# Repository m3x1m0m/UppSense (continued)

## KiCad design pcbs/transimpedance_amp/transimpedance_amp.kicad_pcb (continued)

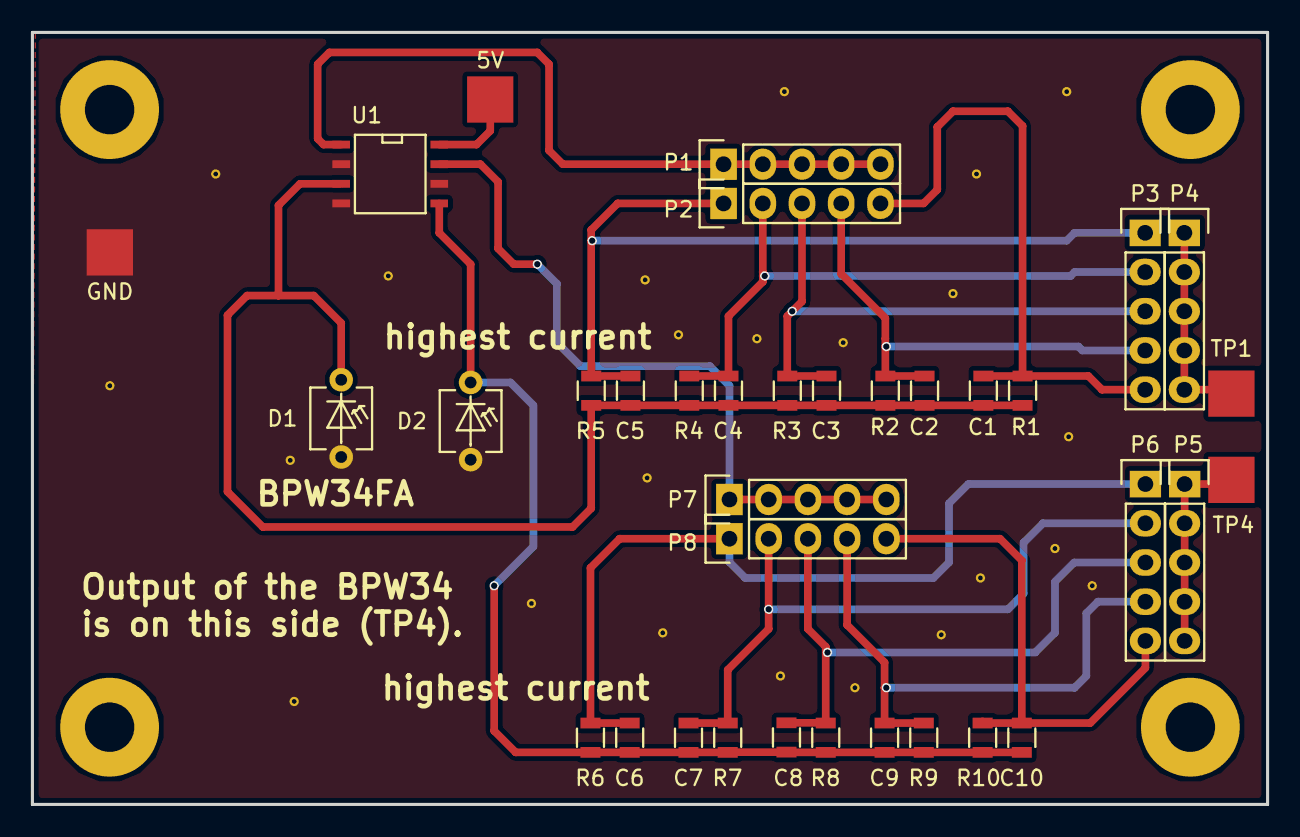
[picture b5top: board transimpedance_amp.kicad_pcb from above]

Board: 2 copper layers, 80.0 x 50.0 mm, 35 parts (0 on the bottom side), 18 nets.

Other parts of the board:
5V: TEST; TP_SMD_quadr_3mm
GND: TEST; TP_SMD_quadr_3mm

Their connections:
+5V: 5V.1; also elsewhere on the board
GND: GND.1; also elsewhere on the board

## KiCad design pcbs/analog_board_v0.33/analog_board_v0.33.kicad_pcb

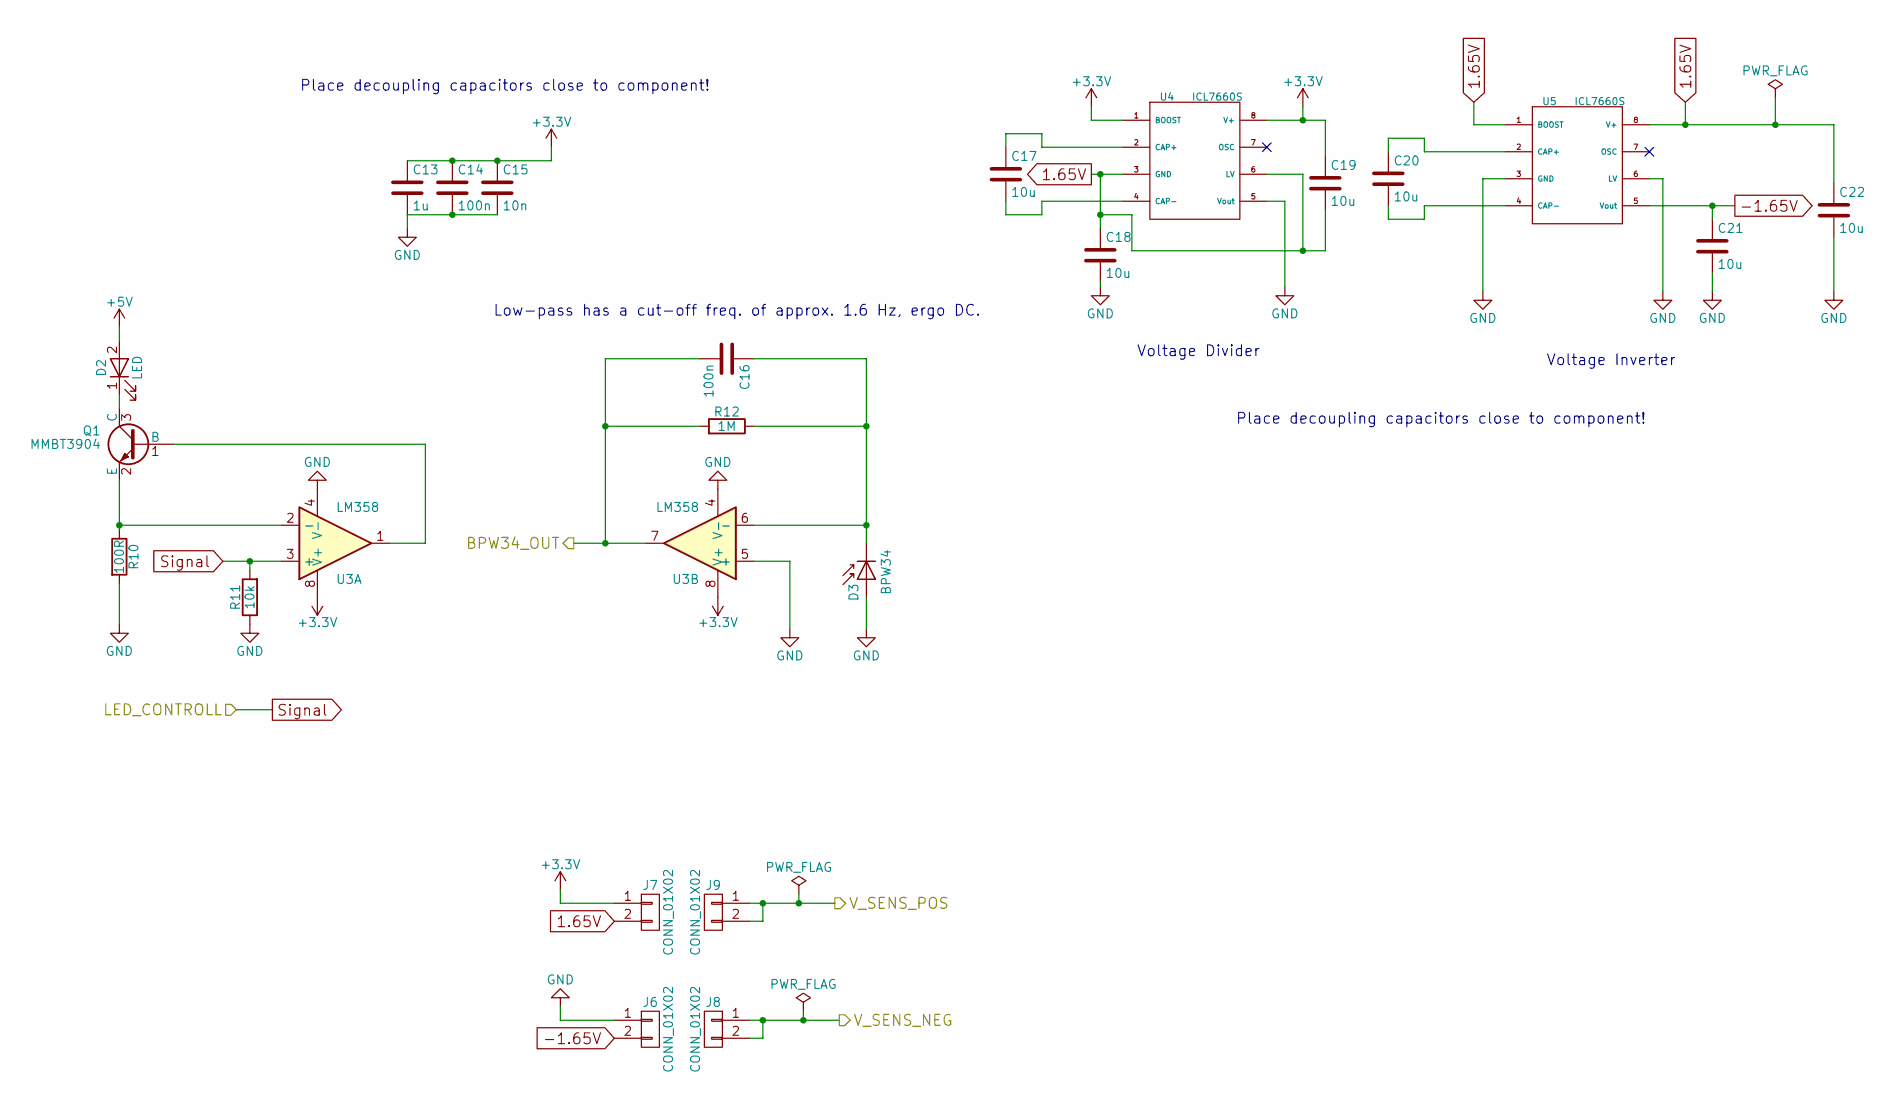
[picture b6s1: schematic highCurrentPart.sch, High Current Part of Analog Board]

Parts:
C13: 1u; R_0805; Farnell 2496946
C14, C16: 100n; R_0805; Farnell 499687
C15: 10n; R_0805; Farnell 1414662
C17, C18, C19, C20, C21, C22: 10u; R_0805; Farnell 1833812
D2: LED; LED_D5.0mm
D3: BPW34; BPW34FA; Farnell 1045425
J6, J7, J8, J9: CONN_01X02; Samtec-PHT-1-2-01-L-S
Q1: MMBT3904; SOT-23; Farnell 1757935
R10: 100R; R_0805; Farnell 9237364
R11: 10k; R_0805; Farnell 9237755
R12: 1M; R_0805; Farnell 1576507
U3: LM358; SOIC-8-N; Farnell 1564331
U4, U5: ICL7660S; SOIC-8-N; Farnell 1561969

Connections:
1.65V: C18.1, C19.2, C22.1, J7.2, U4.3 (GND), U4.6 (LV), U5.1 (BOOST), U5.8 (V+)
+3V3: C13.1, C14.1, C15.1, C19.1, J7.1, U3.8 (V+), U4.1 (BOOST), U4.8 (V+); also elsewhere on the board
+5V: D2.2 (A); also elsewhere on the board
-1.65V: C21.1, J6.2, U5.5 (Vout)
/highCurrentPart/V_SENS_NEG: J8.1, J8.2; also elsewhere on the board
/highCurrentPart/V_SENS_POS: J9.1, J9.2; also elsewhere on the board
/interface/ADC4: C16.2, R12.2, U3.7; also elsewhere on the board
GND: C13.2, C14.2, C15.2, C18.2, C21.2, C22.2, D3.2 (A), J6.1, R10.2, R11.1, U3.4 (V-), U3.5 (+), U4.5 (Vout), U5.3 (GND), U5.6 (LV); also elsewhere on the board
unnamed: C16.1, D3.1 (K), R12.1, U3.6 (-)
unnamed: C17.1, U4.2 (CAP+)
unnamed: C17.2, U4.4 (CAP-)
unnamed: C20.1, U5.2 (CAP+)
unnamed: C20.2, U5.4 (CAP-)
unnamed: D2.1 (K), Q1.3 (C)
unnamed: Q1.1 (B), U3.1
unnamed: Q1.2 (E), R10.1, U3.2 (-)
Signal: R11.2, U3.3 (+); also elsewhere on the board

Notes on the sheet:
Place decoupling capacitors close to component!
Low-pass has a cut-off freq. of approx. 1.6 Hz, ergo DC.
Voltage Inverter
Voltage Divider

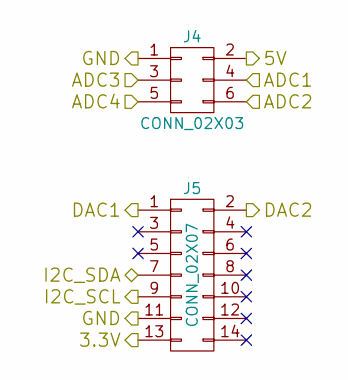
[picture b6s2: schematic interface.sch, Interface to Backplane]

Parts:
J4: CONN_02X03; Pin_Header_Angled_2x03_Pitch2.54mm
J5: CONN_02X07; Pin_Header_Angled_2x07_Pitch2.54mm

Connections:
+3V3: J5.13; also elsewhere on the board
+5V: J4.2, J4.3; also elsewhere on the board
/interface/ADC1: J4.4; also elsewhere on the board
/interface/ADC2: J4.6; also elsewhere on the board
/interface/ADC4: J4.5; also elsewhere on the board
/interface/DAC2: J5.2; also elsewhere on the board
/interface/I2C_SCL: J5.9; also elsewhere on the board
/interface/I2C_SDA: J5.7; also elsewhere on the board
GND: J4.1, J5.11; also elsewhere on the board
Signal: J5.1; also elsewhere on the board

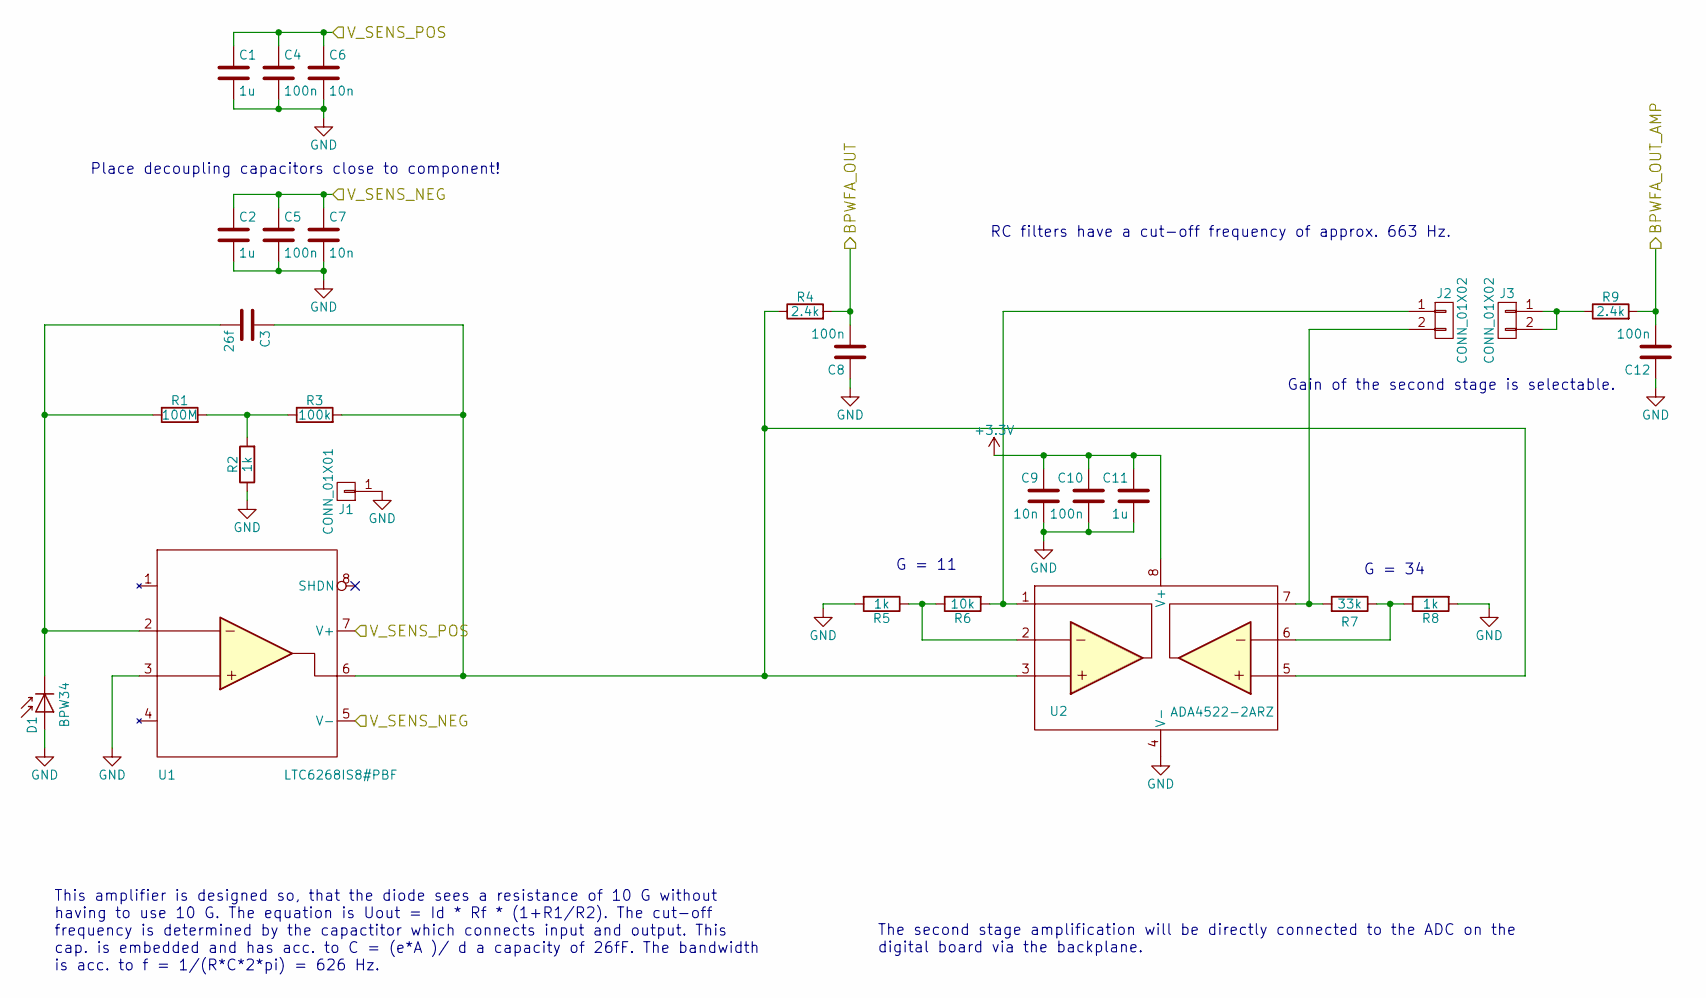
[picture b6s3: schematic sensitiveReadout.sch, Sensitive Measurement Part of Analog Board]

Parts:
C1, C2, C11: 1u; R_0805; Farnell 2496946
C3: 26f; EMBEDDED_CAP_1mm
C4, C5, C8, C10, C12: 100n; R_0805; Farnell 499687
C6, C7, C9: 10n; R_0805; Farnell 1414662
D1: BPW34; BPW34FA_w_Silks; Farnell 1045425
J1: CONN_01X01; GuardConnector
J2, J3: CONN_01X02; Samtec-PHT-1-2-01-L-S
R1: 100M; R_0805_W_Silks; Farnell 9236511
R2: 1k; R_0805_W_Silks; Farnell 9237496
R3: 100k; R_0805_W_Silks; Farnell 2447551
R4, R9: 2.4k; R_0805; Farnell 2502703
R5, R8: 1k; R_0805; Farnell 9237496
R6: 10k; R_0805; Farnell 9237755
R7: 33k; R_0805; Farnell 2078965
U1: LTC6268IS8#PBF; SOIC-8-N-W-Silks; Farnell 2464182
U2: ADA4522-2ARZ; SOIC-8-N; Farnell 2505560

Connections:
+3V3: C9.1, C10.1, C11.1, U2.8 (V+); also elsewhere on the board
/highCurrentPart/V_SENS_NEG: C2.1, C5.1, C7.1, U1.5 (V-); also elsewhere on the board
/highCurrentPart/V_SENS_POS: C1.1, C4.1, C6.1, U1.7 (V+); also elsewhere on the board
/interface/ADC1: C8.2, R4.2; also elsewhere on the board
/interface/ADC2: C12.2, R9.2; also elsewhere on the board
GND: C1.2, C2.2, C4.2, C5.2, C6.2, C7.2, C8.1, C9.2, C10.2, C11.2, C12.1, D1.2 (A), J1.1, R2.1, R5.2, R8.2, U1.3, U2.4 (V-); also elsewhere on the board
unnamed: C3.1, R3.2, R4.1, U1.6, U2.3, U2.5
unnamed: C3.2, D1.1 (K), R1.1, U1.2
unnamed: J2.1, R6.2, U2.1
unnamed: J2.2, R7.2, U2.7
unnamed: J3.1, J3.2, R9.1
unnamed: R1.2, R2.2, R3.1
unnamed: R5.1, R6.1, U2.2
unnamed: R7.1, R8.1, U2.6

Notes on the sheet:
Place decoupling capacitors close to component!
The second stage amplification will be directly connected to the ADC on the digital board via the backplane.
RC filters have a cut-off frequency of approx. 663 Hz.
This amplifier is designed so, that the diode sees a resistance of 10 G without having to use 10 G. The equation is Uout = Id * Rf * (1+R1/R2). The cut-off frequency is determined by the capactitor which connects input and output. This cap. is embedded and has acc. to C = (e*A )/ d a capacity of 26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
G = 11
G = 34
Gain of the second stage is selectable.

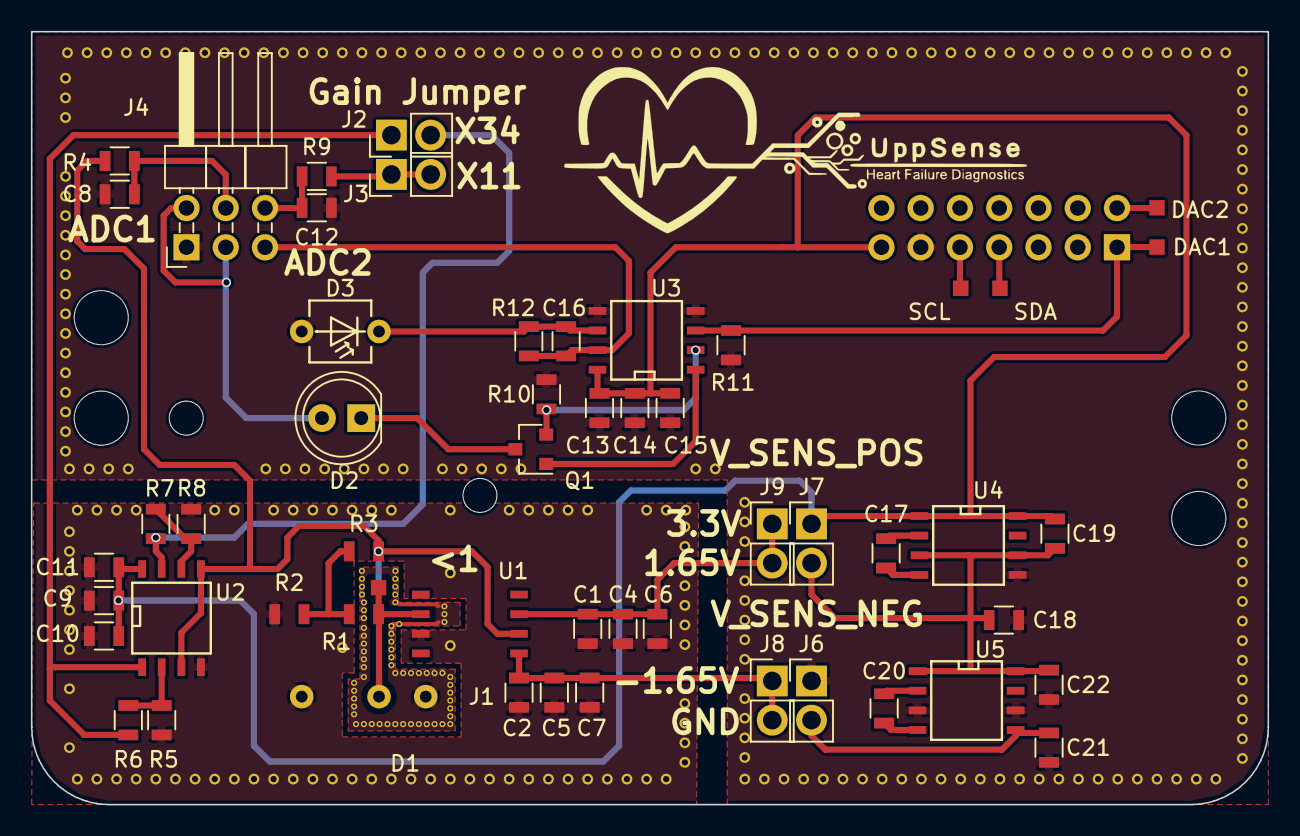
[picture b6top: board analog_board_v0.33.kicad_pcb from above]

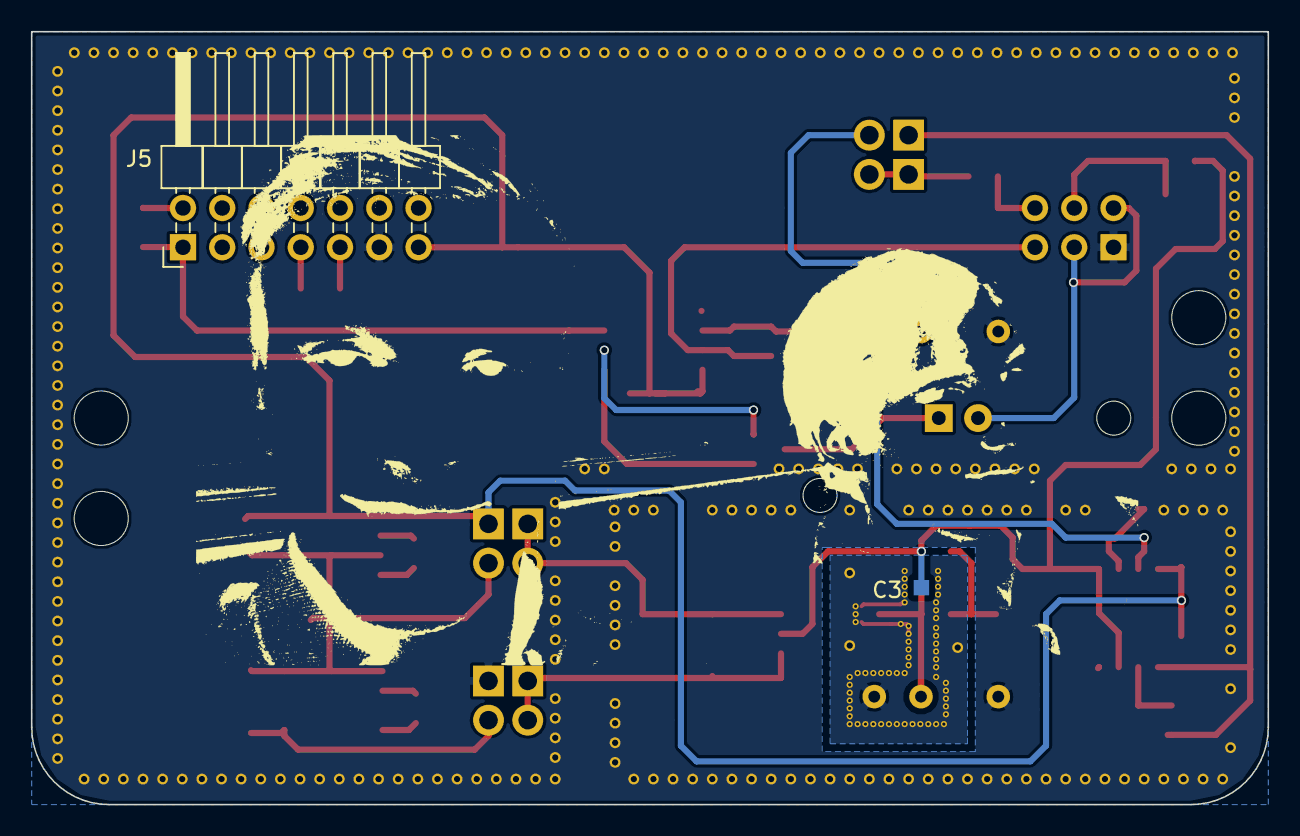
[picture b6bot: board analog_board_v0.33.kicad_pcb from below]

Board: 2 copper layers, 80.0 x 50.0 mm, 56 parts (2 on the bottom side), 30 nets.

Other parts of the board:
DAC1: DAC1; TP_SMD_quadr_1mm
DAC2: DAC2; TP_SMD_quadr_1mm
SCL: TEST; TP_SMD_quadr_1mm
SDA: TEST; TP_SMD_quadr_1mm

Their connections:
/interface/DAC2: DAC2.1; also elsewhere on the board
/interface/I2C_SCL: SCL.1; also elsewhere on the board
/interface/I2C_SDA: SDA.1; also elsewhere on the board
Signal: DAC1.1; also elsewhere on the board

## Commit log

2017-02-07 First commit :D
2017-03-26 Added a research plan for the egineering team.
2017-03-28 Small adjustments and clarifcation of the price breakdown
2017-03-31 Worked on the project plan.
2017-04-03 Project plan ready.
2017-04-10 Added papers.
2017-04-10 Added a opamp model.
2017-04-11 Added aditional trans. amp. simulations for other currents.
2017-04-11 Found another opam AD8616. Added model.
2017-04-12 Current source
2017-04-12 Some old documents
2017-04-13 More stuff.
2017-04-13 Updated shopping list.
2017-04-13 completion of the current bom
2017-04-13 Simulated and added raw simulation for RC filter.
2017-04-13 proper
2017-04-13 completed bom
2017-04-13 start with pcb
2017-04-13 gitignore
2017-04-13 Better gitignore
2017-04-13 New .gitignore which takes LTSpice into account.
2017-04-13 Current source pcb
2017-04-13 lt spice
2017-04-18 Adding a CAD file.
2017-04-24 Started layouting prototype v0.1.
2017-04-25 Done with layouting so far.
2017-04-25 Finished layout of transimpedance amplifier.
2017-04-25 Current source simulation
2017-04-25 Almost finished first version pcb
2017-04-25 added right angle
2017-04-25 Finished the first pcb
2017-04-25 Removed components in inventory
2017-04-26 Started with housing. It is already nice.
2017-04-26 Quite far with the housing.
2017-04-27 Fixed a couple of bugs in the open box module. Now it is bravo.
2017-04-27 Almost done with the design.
2017-04-28 Housing ready for first experiments.
2017-04-28 Forgot to add some stuff.
2017-04-28 Found a design error. Has to be corrected.
2017-05-01 Finished layout. Sill room for optimization.
2017-05-01 Finished transimpedance amp. layout. Produced output for v0.1.
2017-05-01 Cleaned up a bit.
2017-05-01 Added output.
2017-05-01 Cleaning.
2017-05-03 Started project for etching.
2017-05-03 Changed list.
2017-05-03 Added budget.
2017-05-03 Not needed
2017-05-03 Rev.1 + Gerbers
2017-05-03 Created gerber files.
2017-05-08 Orders for etching added.
2017-05-13 Produced some nice pcitures for brochure.
2017-05-18 Changed allowances to mostly 0.2 mm. Made walls thicker.
2017-05-23 Optimized some stuff. Hope to be bug free now.
2017-06-07 Finished drill press adapter.
2017-06-08 Simulated a LED driver for the UV lamp.
2017-06-09 Finished a PCB holder for etching.
2017-06-09 STLs.
2017-06-09 Cleaned up.
2017-06-10 Improved the PCB holder.
2017-06-12 Finished etching machine design.
2017-06-12 Added a floor protection for cuvette. One doublecheck left.
2017-06-13 Simulation done for today.
2017-06-13 Started layouting new board.
2017-06-13 Cleaning
2017-06-14 Finished the new analog board.
2017-06-14 Added some mounting holes.
2017-06-17 Almost done with the etching machine CAD work.
2017-06-20 Started working on a backplane.
2017-06-20 Adding schematics as PDF.
2017-06-22 Small adoptions for the glass silde to be put on the analog PCB directly.
2017-06-22 Made the LED illuminator a little bit smaller.
2017-06-25 Updated electrical spec.
2017-06-25 Mechanical specs updated.
2017-06-25 Updated mates.
2017-06-25 Changed electrical spec again.
2017-06-26 Schematics of backplane done.
2017-06-26 Came quite far with backplane design. Not finished yet.
2017-06-27 Backplane version 1 ready.
2017-06-28 Simulated a lot today. Ideas for the new transimpedance amp. are there.
2017-06-28 digital_board
2017-06-29 Simulated the new transimpedance amp.
2017-06-30 Finished schematics of the analog_board_v0.2 today.
2017-07-02 Added some iportant backplane spec.
2017-07-02 Resolved issue where the pins to the backboard were flipped
2017-07-03 Analog board basically finished.
2017-07-04 Small changes on the backplane standing out.
2017-07-04 Backplane definitely finished. Somethings wrong with TIA. Has to be checked tomorrow.
2017-07-05 Finished the photo extender, backplane and the analog board.
2017-07-05 Added BOMs and gerber files.
2017-07-06 Four boards in less than two weeks :D
2017-07-08 Release Candidate 1. moved headers, added RC filters
2017-07-08 Reverted header
2017-07-09 added temp sensor Added Gerbers
2017-07-09 Mechanics developed further.
2017-07-10 Updated BOM.
2017-07-10 Updated bom with some of the logic components
2017-07-10 Finalized BOM, ESP and DAC are missing on farnel
2017-07-11 Worked on emchnaics.
2017-07-11 Modified BOM.
2017-07-12 drill files
2017-07-13 Poor Elmar.
2017-07-22 Removed tenting from the ic's. Sorry! shifted one connector
2017-07-28 Box seems to be finished.
2017-07-28 Housing finished. Final checks outstanding.
2017-07-29 Housing finished. STLs produced.
2017-07-29 Finished glass slide holder.
2017-07-29 Forgot sth.
2017-07-31 Made meachnical design better for FDM.
2017-08-01 Final checks and rotating.
2017-08-02 Updated the glass slide holder.
2017-08-02 Small test
2017-08-07 Started working on mechanics rev 5.
2017-08-07 Modified the mechanics a bit to be able to print everything once more.
2017-08-07 Added a web interface, with strange behavior? Tomorrow fixing the bugs
2017-08-08 Changed logging, added addresses on top of application
2017-08-08 Wrong integer size
2017-08-08 Fixed wrong conversion
2017-08-08 Cleaned a bit and added a .gitignore.
2017-08-08 Started with the DAC driver.
2017-08-09 Fixed conversion bug. Adjusted reading setting adc
2017-08-09 Driver for DAC works. Started with an application objectfor LED controll.
2017-08-09 Continued programming for a bit ..
2017-08-09 Made it a bit more elegant
2017-08-09 Removed stupid debnugging
2017-08-09 Added printout of settings. Made the adc freespinning
2017-08-11 I have no idea what I'm doin.
2017-08-11 Fix for the revision 1 channels
2017-08-11 Renamed channels
2017-08-11 Screenshots.
2017-08-14 Made rectangle signal from DAC work.
2017-08-15 Fixed minor problem with one ADC not showing up.
2017-08-15 Documented my code. Added a doxygen file.
2017-08-15 Minor correction.
2017-08-16 Solved inaccuracy problem with adc. Started with a nice overview for the raw samples
2017-08-16 Lets set this fixed. maybe move it to 10.0.0.1 in the future?
2017-08-16 Worked on the analog PCB v0.33.
2017-08-16 Ported to 3v3
2017-08-21 Ananlog v0.33 is ready.
2017-08-21 refactored pcb structure added rev 2
2017-08-21 Added Elmars PCB to the master branch.
2017-08-21 Finished new BOM.
2017-08-22 Started with a signal processor.
2017-08-22 Reworked the architecture to allow for a publisher/subscriber model. Added signal processing. Make sure to stop the hub before changing channels! (To be done automatically in the future) and there is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
2017-08-23 User interface works. Have to redo the communication, step away from string compares, and get nice json.
2017-08-23 Saves to file on pressing stop now
2017-08-23 some code refactoring
2017-08-23 refactoring continues
2017-08-23 Something always has to go wrong
2017-08-23 Further cleaning of the code
2017-08-23 Updated the BOM.
2017-08-23 Fixed includes
2017-08-23 This should work
2017-08-24 Try the faster adc
2017-08-25 Some adaptions for the experiments.
2017-08-26 Created some stuff for docs and optimized mechanics.
2017-08-27 Tested FFT library.
2017-08-28 Refactored. Removed stupid debugging. Pressing start will now sample for one second
2017-08-28 Edited the illuminator, so it fits the new PCB.
2017-08-28 Added README.md.
2017-08-29 Reworked buffering structure
2017-09-03 Added proper support for rev2
2017-09-04 Presentation translational pitch added.
2017-09-04 Updated block diagram for HW.
2017-09-06 Documentation.
2017-09-19 Updated the README.
2017-09-23 Edited README.md
2017-10-16 Presentation
